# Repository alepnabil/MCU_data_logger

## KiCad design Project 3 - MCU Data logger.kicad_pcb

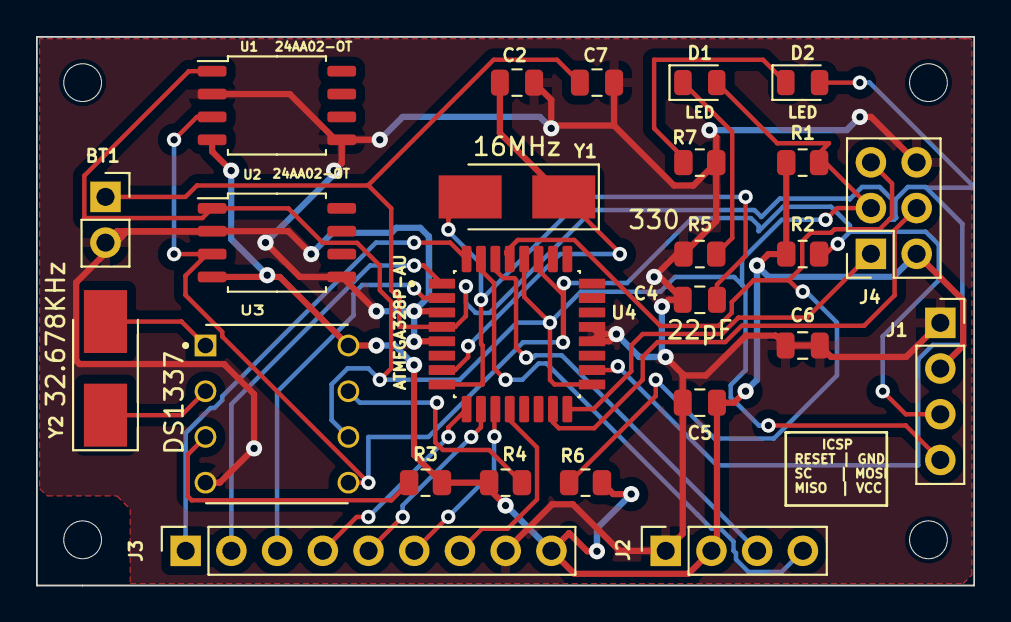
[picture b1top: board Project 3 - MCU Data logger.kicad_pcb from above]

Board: 2 copper layers, 52.1 x 30.5 mm, 29 parts (0 on the bottom side), 25 nets.

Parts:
BT1: Battery; PinSocket_1x02_P2.54mm_Vertical
C2, C4: 22pF; C_0805_2012Metric
C5: 0.1u; C_0805_2012Metric
C6: C; C_0805_2012Metric
C7: 100nF; C_0805_2012Metric
D1, D2: LED; LED_0805_2012Metric
H1, H2, H3, H4: MountingHole; MountingHole_2.1mm
J1, J2: Conn_01x04_Pin; PinSocket_1x04_P2.54mm_Vertical
J3: Conn_01x09_Pin; PinSocket_1x09_P2.54mm_Vertical
J4: Conn_02x03_Odd_Even; PinSocket_2x03_P2.54mm_Vertical
R1, R2: 4.7K; R_0805_2012Metric
R3, R4, R6: 10K; R_0805_2012Metric
R5, R7: 330; R_0805_2012Metric
U1, U2: 24AA02-OT; SOIC-8_5.23x5.23mm_P1.27mm
U3: DS1337; DIP794W47P254L991H457Q8
U4: ATMEGA328P-AU; QFP80P900X900X120-32N
Y1: 16MHz; Crystal_SMD_5032-2Pin_5.0x3.2mm_HandSoldering
Y2: 32.678KHz; Crystal_SMD_5032-2Pin_5.0x3.2mm_HandSoldering

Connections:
/D2: J3.1, U4.32 (PD2)
/D3: J3.2, U4.1 (PD3)
/D4: J3.3, U4.2 (PD4)
/D5: J3.4, U4.9 (PD5)
/D6: J3.5, U4.10 (PD6)
/D7: J3.6, U4.11 (PD7)
/D8: J3.7, U4.12 (PB0)
/MISO: J4.1, U4.16 (PB4)
/MOSI: J4.4, U4.15 (PB3)
/RESET: J4.5, R6.2, U4.29 (PC6/~RESET)
/RX: J2.3, U4.30 (PD0)
/SCL: D1.2 (A), J1.4, J4.3, R1.2, U1.1 (SCL), U2.1 (SCL), U3.6 (SCL), U4.17 (PB5), U4.28 (PC5)
/SDA: J1.3, R2.2, U1.3 (SDA), U2.3 (SDA), U3.5 (SDA), U4.27 (PC4)
/TX: J2.4, U4.31 (PD1)
GND: BT1.2 (-), C2.1, C4.1, C5.2, C6.1, C6.2, C7.2, J1.1, J2.1, J3.8, J4.6, R5.1, R7.2, U1.2 (V_{SS}), U1.5 (WP), U2.2 (V_{SS}), U2.5 (WP), U3.4 (GND), U4.3 (GND), U4.5 (GND), U4.20 (AREF), U4.21 (GND)
unnamed: BT1.1 (+), C7.1, D2.2 (A), U4.4 (VCC), U4.18 (AVCC)
unnamed: D1.1 (K), R5.2
unnamed: D2.1 (K), R7.1
unnamed: R3.2, U3.3 (#INTA)
unnamed: R4.2, U3.7 (SQW/#INTB)
unnamed: U3.1 (X1), Y2.2
unnamed: U3.2 (X2), Y2.1
unnamed: C2.2, U4.7 (PB6), Y1.1
unnamed: C4.2, U4.8 (PB7), Y1.2
VCC: C5.1, J1.2, J2.2, J3.9, J4.2, R1.1, R2.1, R3.1, R4.1, R6.1, U1.4 (V_{CC}), U2.4 (V_{CC}), U3.8 (VCC)

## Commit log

2024-02-18 added initial files
2024-02-18 add clock and microcontroller symbols
2024-02-18 wire up timer,eeprom,mcu
2024-02-19 added wiring for second sheet
2024-02-19 add comments and netclass for power
2024-02-19 setup pcbnew
2024-02-19 added intial routing
2024-02-20 added routing
2024-02-20 add silkscreen and improve text
2024-02-21 add text and graphics
2024-02-21 add 3d model
